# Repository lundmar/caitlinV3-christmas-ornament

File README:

CaitlinV3 X-mas Tree

Created with Kicad 5.15.

This work is licensed under a Creative Commons Attribution 4.0 International License.

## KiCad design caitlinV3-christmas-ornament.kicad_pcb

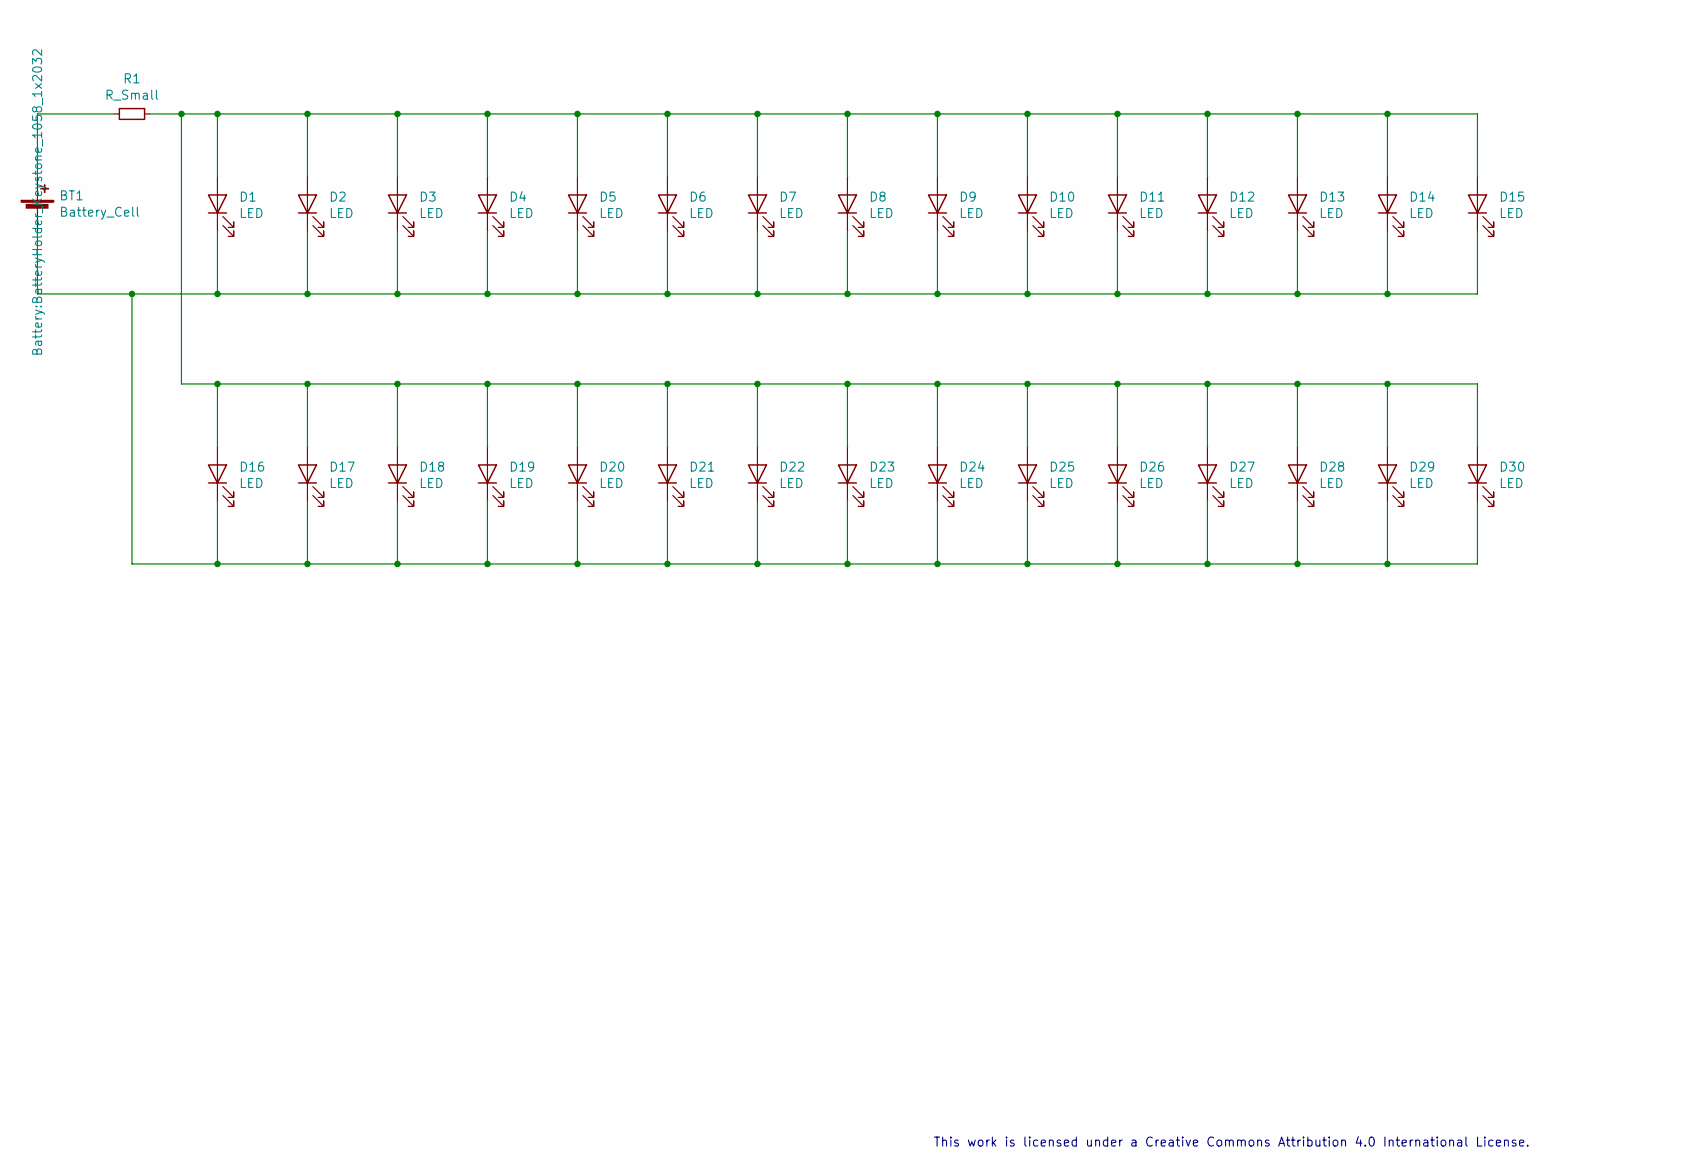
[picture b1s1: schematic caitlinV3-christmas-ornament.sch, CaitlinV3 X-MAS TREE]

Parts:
BT1: Battery_Cell; BatteryHolder_Keystone_1058_1x2032
D1, D2, D3, D4, D5, D6, D7, D8, D9, D10, D11, D12, D13, D14, D15, D16, D17, D18, D19, D20, D21, D22, D23, D24, D25, D26, D27, D28, D29, D30: LED; LED_0805_2012Metric
R1: R_Small; R_0805_2012Metric

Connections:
unnamed: BT1.1 (+), R1.2
unnamed: BT1.2 (-), D1.1 (K), D2.1 (K), D3.1 (K), D4.1 (K), D5.1 (K), D6.1 (K), D7.1 (K), D8.1 (K), D9.1 (K), D10.1 (K), D11.1 (K), D12.1 (K), D13.1 (K), D14.1 (K), D15.1 (K), D16.1 (K), D17.1 (K), D18.1 (K), D19.1 (K), D20.1 (K), D21.1 (K), D22.1 (K), D23.1 (K), D24.1 (K), D25.1 (K), D26.1 (K), D27.1 (K), D28.1 (K), D29.1 (K), D30.1 (K)
unnamed: D1.2 (A), D2.2 (A), D3.2 (A), D4.2 (A), D5.2 (A), D6.2 (A), D7.2 (A), D8.2 (A), D9.2 (A), D10.2 (A), D11.2 (A), D12.2 (A), D13.2 (A), D14.2 (A), D15.2 (A), D16.2 (A), D17.2 (A), D18.2 (A), D19.2 (A), D20.2 (A), D21.2 (A), D22.2 (A), D23.2 (A), D24.2 (A), D25.2 (A), D26.2 (A), D27.2 (A), D28.2 (A), D29.2 (A), D30.2 (A), R1.1

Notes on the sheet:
This work is licensed under a Creative Commons Attribution 4.0 International License.

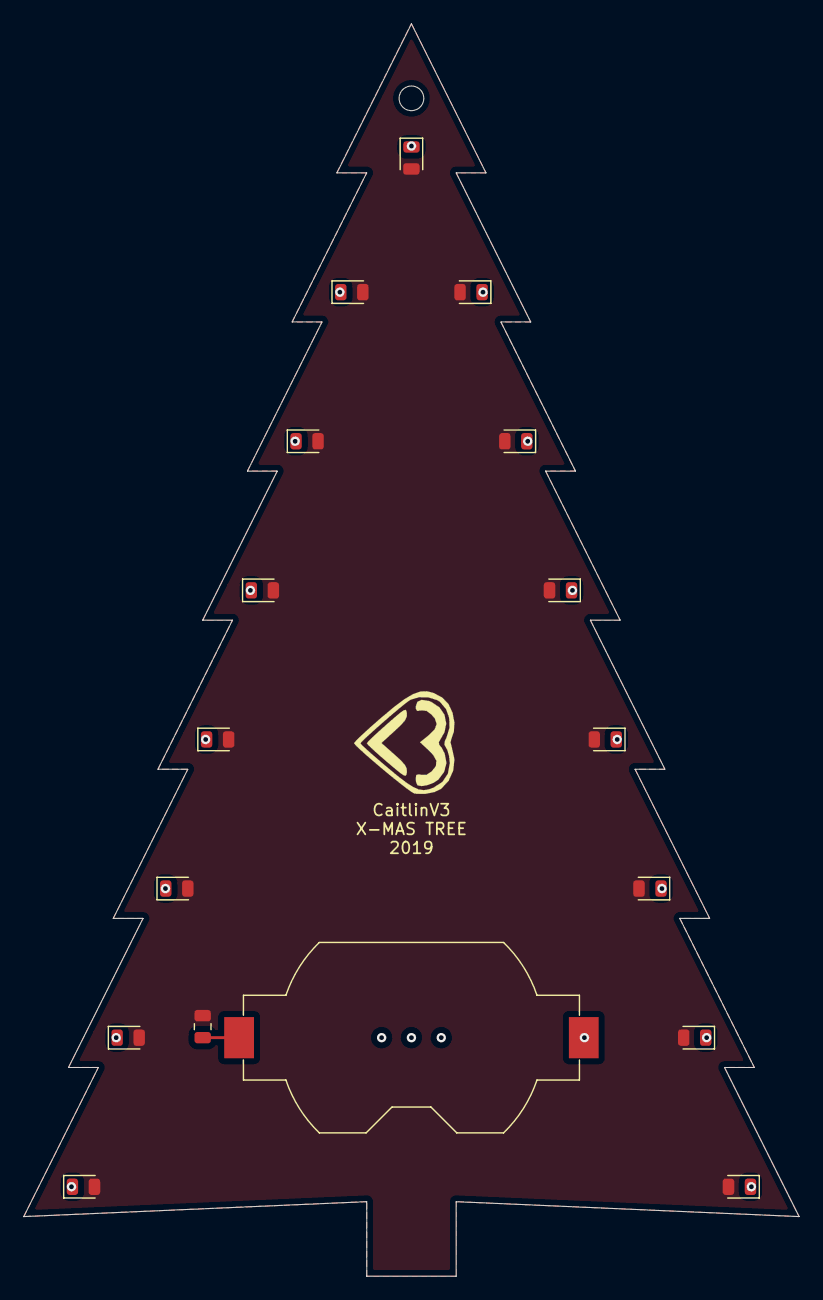
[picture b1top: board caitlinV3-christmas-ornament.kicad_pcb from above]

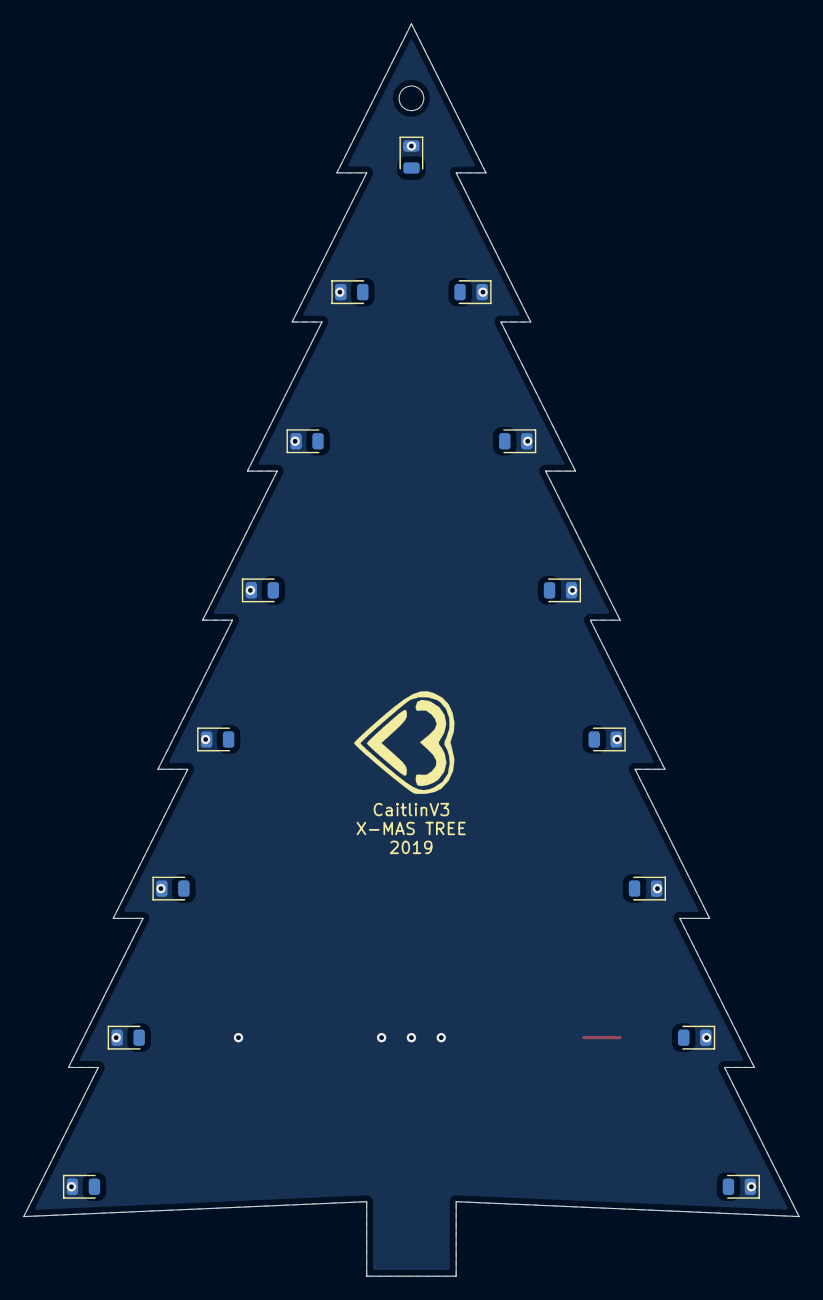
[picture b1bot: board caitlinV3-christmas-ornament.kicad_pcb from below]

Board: 2 copper layers, 66.0 x 106.7 mm, 32 parts (15 on the bottom side), 3 nets.

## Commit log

2019-12-13 Initial import
2019-12-14 Created images folder
2019-12-14 Add README
